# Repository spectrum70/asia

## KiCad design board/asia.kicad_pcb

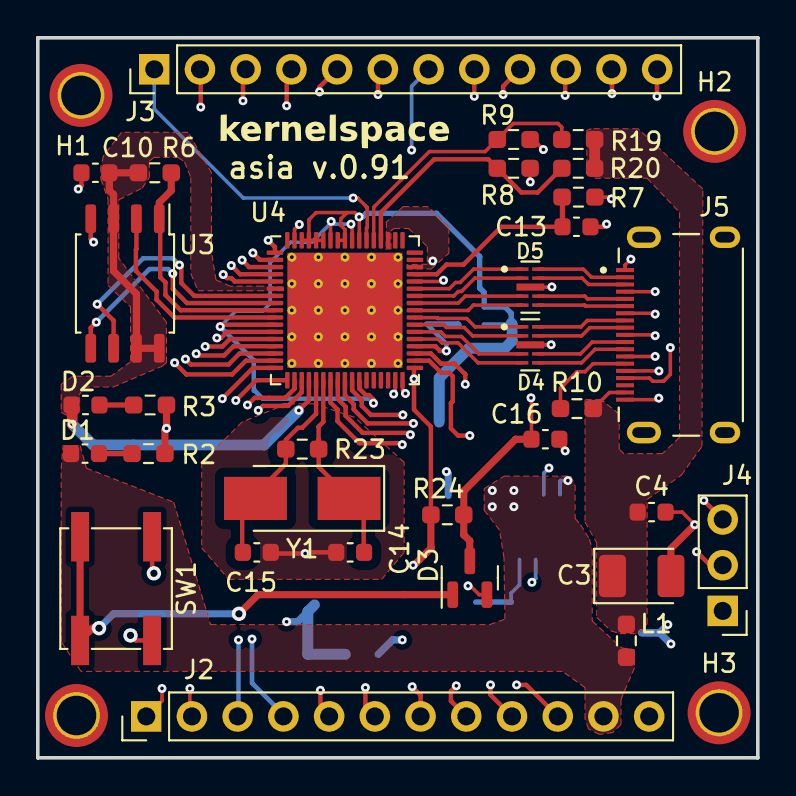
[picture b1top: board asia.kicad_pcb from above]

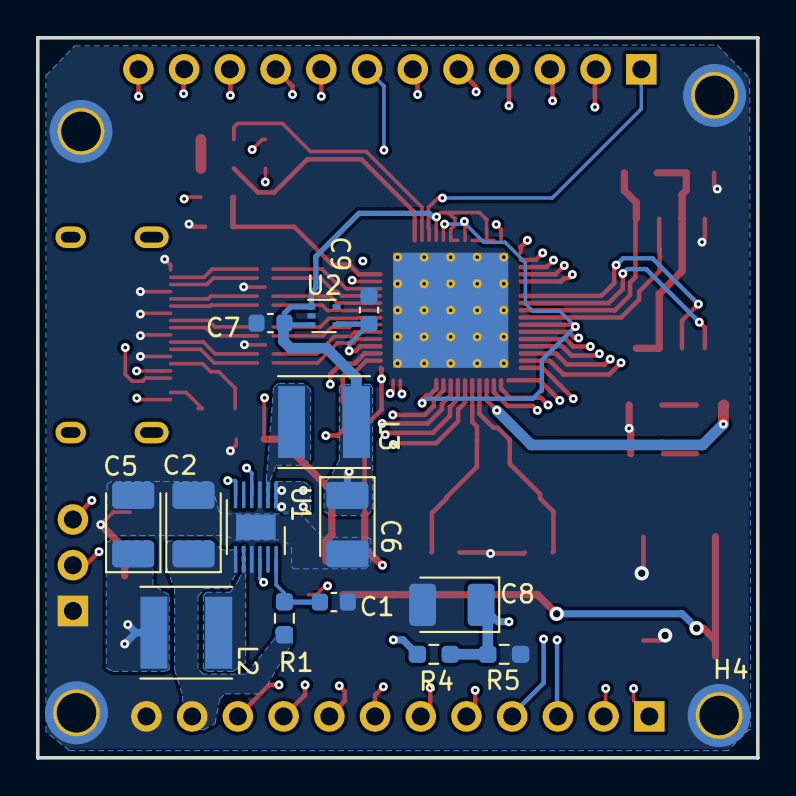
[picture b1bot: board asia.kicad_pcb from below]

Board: 4 copper layers, 40.0 x 40.0 mm, 50 parts (15 on the bottom side), 67 nets.

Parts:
C1, C4, C7, C9, C13: 100n; C_0603_1608Metric
C2, C3, C5, C6, C8: 10u; CP_EIA-3528-21_Kemet-B_Pad1.50x2.35mm_HandSolder
C10: 100nF; C_0603_1608Metric
C14, C15, C16: 20pF; C_0603_1608Metric
D1, D2: LED; C_0603_1608Metric
D3: BAT54A; SOT-23
D4, D5: RCLAMP0524PATCT; asia-clamp
H1, H2, H3, H4: MountingHole_Pad; MountingHole_2.2mm_M2_ISO7380_Pad_TopBottom
J2, J3: Conn_01x12_Pin; PinHeader_1x12_P2.54mm_Vertical
J4: Conn_01x03_Pin; PinHeader_1x03_P2.54mm_Vertical
J5: HDMI_C_1.3; asia-hdmi
L1: 100R; R_0603_1608Metric_Pad0.98x0.95mm_HandSolder
L2, L3: 4.7u 2A; L_Taiyo-Yuden_NR-50xx
R1: 100K 1%; R_0603_1608Metric_Pad0.98x0.95mm_HandSolder
R2: 270; R_0603_1608Metric_Pad0.98x0.95mm_HandSolder
R3: 100; R_0603_1608Metric_Pad0.98x0.95mm_HandSolder
R4, R8, R9: 33; R_0603_1608Metric_Pad0.98x0.95mm_HandSolder
R5: 1K; R_0603_1608Metric_Pad0.98x0.95mm_HandSolder
R6, R19, R20, R24: 4K7; R_0603_1608Metric_Pad0.98x0.95mm_HandSolder
R7, R10: 10K; R_0603_1608Metric_Pad0.98x0.95mm_HandSolder
R23: 1M; R_0603_1608Metric_Pad0.98x0.95mm_HandSolder
SW1: SW_Push; SW_SPST_EVQP0
U1: PAM2306AYPKE; WDFN-12-1EP_3x3mm_P0.45mm_EP1.7x2.5mm
U2: TCR2EE11; SOT-553
U3: W25Q128JVS; SOIC-8_5.23x5.23mm_P1.27mm
U4: nationalchip_GX6605S; QFN-68-1EP_8x8mm_P0.4mm_EP6.4x6.4mm_ThermalVias
Y1: 12Mhz; Crystal_SMD_5032-2Pin_5.0x3.2mm_HandSoldering

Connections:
+1V1: C9.1, U2.4 (VOUT), U4.11 (VDD11), U4.28 (ADCAVDD11/PLLVDD11/VDD11), U4.38 (VDD11), U4.59 (PLLVDD11), U4.62 (VDD11_DDR)
+1V8: C6.1, C7.1, L3.2, U1.10 (FB2), U2.1 (CTRL), U2.3 (VIN), U4.58 (VDDIO_DRAM), U4.60 (VDD_DATA), U4.61 (VDDIO_DATA), U4.63 (VDDIO_CLK), U4.64 (VDDIO_CMD), U4.65 (VDDIO_CMD), U4.66 (VDDIO_DRAM)
+2V5: C8.1, R4.2, R5.1, U4.47 (AVDD25)
+3V3: C5.1, C10.1, D2.2 (A), L2.2, R4.1, R6.1, R24.1, U1.4 (FB1), U3.3 (IO2), U3.7 (IO3), U3.8 (VCC), U4.6 (VDD33), U4.21 (VDD33), U4.35 (USBAVDD33), U4.49 (DACAVDD33), U4.54 (VDD33)
+5V: C2.1, D1.2 (A), J2.11, L1.1, R1.1, U1.1 (VIN2), U1.6 (EN1), U1.7 (VIN1)
+5VP: C3.1, C4.1, J5.18 (+5V), L1.2, R10.2, R19.1, R20.1
/cpu/CK+: D4.7, J5.11 (CK+)
/cpu/CK-: D4.6, J5.12 (CK-)
/cpu/D0+: D4.10, J5.8 (D0+)
/cpu/D0-: D4.9, J5.9 (D0-)
/cpu/D1+: D5.7, J5.5 (D1+)
/cpu/D1-: D5.6, J5.6 (D1-)
/cpu/D2+: D5.10, J5.2 (D2+)
/cpu/D2-: D5.9, J5.3 (D2-)
/cpu/HDMI_PLG: C13.1, R7.2, U4.48 (HPD)
/cpu/HDMI_SCL: R9.2, R19.2, U4.56 (DDCSCL/PORT19)
/cpu/HDMI_SDA: R8.2, R20.2, U4.55 (DDCSDA/PORT18)
/cpu/JTAG_NRST: D3.2, J3.7
/cpu/PORT0: J3.12, U4.1 (DBGTDI/PORT0)
/cpu/PORT1: J3.11, U4.2 (DBGTDO/PORT1)
/cpu/PORT2: J3.10, U4.3 (DBGTMS/PORT2)
/cpu/PORT3: J3.9, U4.4 (DBGTCK/PORT3)
/cpu/PORT4: J3.8, U4.5 (DBGTRST/PORT4)
/cpu/PORT20: J3.1, U4.57 (SPDIF/PORT20)
/cpu/RESET: C16.1, D3.3, R24.2, U4.67 (RSTN)
/cpu/SPI_CLK: U3.6 (CLK), U4.7 (SPISCK)
/cpu/SPI_CS: R6.2, U3.1 (~CS), U4.9 (SPICSN)
/cpu/SPI_MISO: U3.2 (DO(IO1)), U4.10 (SPIMISO)
/cpu/SPI_MOSI: U3.5 (DI(IO0)), U4.8 (SPIMOSI)
/cpu/TX0_N: D4.2, U4.41 (TX0_N)
/cpu/TX0_P: D4.1, U4.42 (TX0_P)
/cpu/TX1_N: D5.5, U4.43 (TX1_N)
/cpu/TX1_P: D5.4, U4.44 (TX1_P)
/cpu/TX2_N: D5.2, U4.45 (TX2_N)
/cpu/TX2_P: D5.1, U4.46 (TX2_P)
/cpu/TXC_N: D4.5, U4.39 (TXC_N)
/cpu/TXC_P: D4.4, U4.40 (TXC_P)
/cpu/UART1_RX: J4.3, U4.27 (UART1RX/PORT17)
/cpu/UART1_TX: J4.2, U4.26 (UART1TX/PORT16/AUARTTX)
GND: C1.2, C2.2, C3.2, C4.2, C5.2, C6.2, C7.2, C8.2, C9.2, C10.2, C13.2, C14.2, C15.2, C16.2, D4.3_8, D5.3_8, H1.1, H2.1, H3.1, H4.1, J2.12, J4.1, J5.1 (D2S), J5.4 (D1S), J5.7 (D0S), J5.10 (CKS), J5.13 (GND), R2.2, R3.2, R5.2, SW1.1, U1.3 (GND), U1.9 (GND), U1.13 (GND), U2.2 (GND), U3.4 (GND), U4.69 (GND)
unnamed: D1.1 (K), R2.1
unnamed: D2.1 (K), R3.1
unnamed: D3.1, SW1.2
unnamed: J2.1, U4.34 (USBDM)
unnamed: J2.2, U4.33 (USBDP)
unnamed: J2.3, U4.37 (USB1DM)
unnamed: J2.4, U4.36 (USB1DP)
unnamed: J2.5, U4.17 (DISEQC1/PORT10/TSIDATA5)
unnamed: J2.6, U4.18 (HVSEL/PORT11/TSIDATA6)
unnamed: J2.7, U4.19 (DISEQC0/PORT12/TSIDATA7)
unnamed: J2.8, U4.20 (AGC/PORT13/TSICLK)
unnamed: J2.9, U4.24 (SDA1/PORT14)
unnamed: J2.10, U4.25 (SCL1/PORT15)
unnamed: J3.2, U4.16 (SC1DATA/PORT09/TSIDATA4)
unnamed: J3.3, U4.15 (SC1CD/PORT08/TSIDATA3)
unnamed: J3.4, U4.14 (SC1PWR/PORT07/TSIDATA2)
unnamed: J3.5, U4.13 (SC1RST/PORT06/TSIDATA1)
unnamed: J3.6, U4.12 (SC1CLK/PORT05/TSIDATA0)
unnamed: J5.14 (CEC), R10.1
unnamed: J5.19 (HPD), R7.1
unnamed: J5.15 (SCL), R9.1
unnamed: J5.16 (SDA), R8.1
unnamed: C1.1, R1.2, U1.12 (EN2)
unnamed: L2.1, U1.8 (LX1)
unnamed: L3.1, U1.2 (LX2)
unnamed: C15.1, R23.1, U4.22 (XIN), Y1.2
unnamed: C14.1, R23.2, U4.23 (XOUT), Y1.1

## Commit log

2024-01-13 First initialization
